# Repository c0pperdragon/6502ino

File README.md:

# 6502ino

A minimal circuit to form the environment necessary to run a 65c02 CPU.

Normally getting any form of 6502 processor to run and communicate with the outside
world is very cumbersome. In addition to the CPU and RAM you need very specific 
IO controller parts that can be hooked up to the system address and data bus.
You need a ROM for the initial boot code and some form of MMU to drive the various
selection lines according to the memory address (all IO is memory mapped).
All this leads to a pretty large and costly board even for the most basic 
program to execute.

This project tries to reduce the system size as much as possible by
using a microcontroller - in the form of an Arduino Uno - to do all the
tricky stuff. Together with only a bit of 7400 series logic and 32KB RAM,
this is  enough to get the 65c02 working with 16Mhz on a breadboard.

### Setting the fuses to generate 16Mhz on pin 8

For the setup to work, you need to configure your arduino to permanently
ouput the full system clock on a dedicated pin. This feature can not be set up
from inside a program, but needs to be done by configuring the "fuse bits". 

Setting the fuse bits is a bit complicated, but you only need to do it once. 
To access these bits, you need a dedicated programming device, called the 
AVR ISP (in-circuit-programmer). Luckily any arduino can be programmed to become 
such a device with the "ArduinoISP" example sketch that is included in the 
Arduino IDE. So you basically need a spare arduino for this process.

Wiring up the programmer arduino to the arduino being programmed can be seen in
countless internet resources. But there it is mainly done to programm a bootloader.
You need to do a different thing, for which you need the command-line tool "avrdude.exe"
which is installed along with the Arduino IDE somewhere in the depth of the "hardware/tools"
folder. 

Once everything is hooked up, open a system console and execute the following command (replace com10 
with whatever port your programmer arduino is registered in the system):
```
avrdude -p atmega328p -b 19200 -C ../etc/avrdude.conf -c avrisp -P com10
```

If everything works correctly, this will show you some status and the current settings of the
fuse bits. We are particularly interested in the value of the 'L' fuse bits, which on my
factory default Arduino Uno shows as L:FF. To set the permanent clock output, you need
to modify this value (an 8-bit value) to have the bit 6 set to 0. In my case this means

to set the 'L' fuses to BF:
```
avrdude -p atmega328p -b 19200 -C ../etc/avrdude.conf -c avrisp -P com10 -U lfuse:w:0xBF:m
```

After this settings are done, the Arduino will constantly send a 16Mhz signal on pin 8, 
no matter what, even during reset.

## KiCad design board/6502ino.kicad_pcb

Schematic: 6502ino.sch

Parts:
C1, C2, C3: 100nF; C_Disc_D3.0mm_W1.6mm_P2.50mm
C4: 10uF; C_Disc_D4.3mm_W1.9mm_P5.00mm
JANALOG1: Conn_01x06; PinSocket_1x06_P2.54mm_Vertical
JDIGITAL1: Conn_01x08; PinSocket_1x08_P2.54mm_Vertical
JDIGITAL2: Conn_01x10; PinSocket_1x10_P2.54mm_Vertical
JPOWER1: Conn_01x08; PinSocket_1x08_P2.54mm_Vertical
R1, R2, R3, R4, R5, R6, R7, R8, R9, R10: 6K8; R_Axial_DIN0207_L6.3mm_D2.5mm_P7.62mm_Horizontal
R11: 6k8; R_Axial_DIN0207_L6.3mm_D2.5mm_P7.62mm_Horizontal
R12: 100; R_Axial_DIN0207_L6.3mm_D2.5mm_P7.62mm_Horizontal
U1: W65C02S; DIP-40_W15.24mm_Socket
U2: IDT71256SA; DIP-28_W7.62mm_Socket
U3: 74AC00; DIP-14_W7.62mm_Socket

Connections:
+5V: C1.1, C2.1, C3.1, C4.1, JPOWER1.5, R11.1, U1.4, U1.6, U1.8, U1.36, U2.28, U3.14 (VCC)
/A0: U1.9, U2.10
/A1: U1.10, U2.9
/A2: U1.11, U2.8
/A3: U1.12, U2.21
/A4: U1.13, U2.7
/A5: U1.14, U2.6
/A6: U1.15, U2.23
/A7: U1.16, U2.5
/A8: U1.17, U2.24
/A9: U1.18, U2.25
/A10: U1.19, U2.26
/A11: U1.20, U2.1
/A12: U1.22, U2.2
/A13: U1.23, U2.3
/A14: U1.24, U2.4
/D0: R1.1, U1.33, U2.15
/D1: R2.1, U1.32, U2.16
/D2: R3.1, U1.31, U2.13
/D3: R4.1, U1.30, U2.17
/D4: R5.1, U1.29, U2.12
/D5: R6.1, U1.28, U2.18
/D6: R10.1, U1.27, U2.11
/D7: R9.1, U1.26, U2.19
/IOBUSY: JDIGITAL1.8, R11.2, U3.12
/IOSELECT: R8.1, U1.25, U2.20, U3.13
/PHI2: JDIGITAL2.1, U1.37, U3.4, U3.5, U3.10
/RWB: R7.1, U1.34, U3.1, U3.2
/_RESET: JPOWER1.3, U1.40
GND: C1.2, C2.2, C3.2, C4.2, JDIGITAL2.7, JPOWER1.6, JPOWER1.7, U1.21, U1.38, U2.14, U3.7 (GND)
unnamed: JANALOG1.1, R1.2
unnamed: JANALOG1.2, R2.2
unnamed: JANALOG1.3, R3.2
unnamed: JANALOG1.4, R4.2
unnamed: JANALOG1.5, R5.2
unnamed: JANALOG1.6, R6.2
unnamed: JDIGITAL1.4, R10.2
unnamed: JDIGITAL1.5, R9.2
unnamed: JDIGITAL1.6, R8.2
unnamed: JDIGITAL1.7, R7.2
unnamed: R12.1, U1.2
unnamed: R12.2, U3.11
unnamed: U2.22, U3.6
unnamed: U2.27, U3.8
unnamed: U3.3, U3.9

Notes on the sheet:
(32 KB RAM)
(CPU)

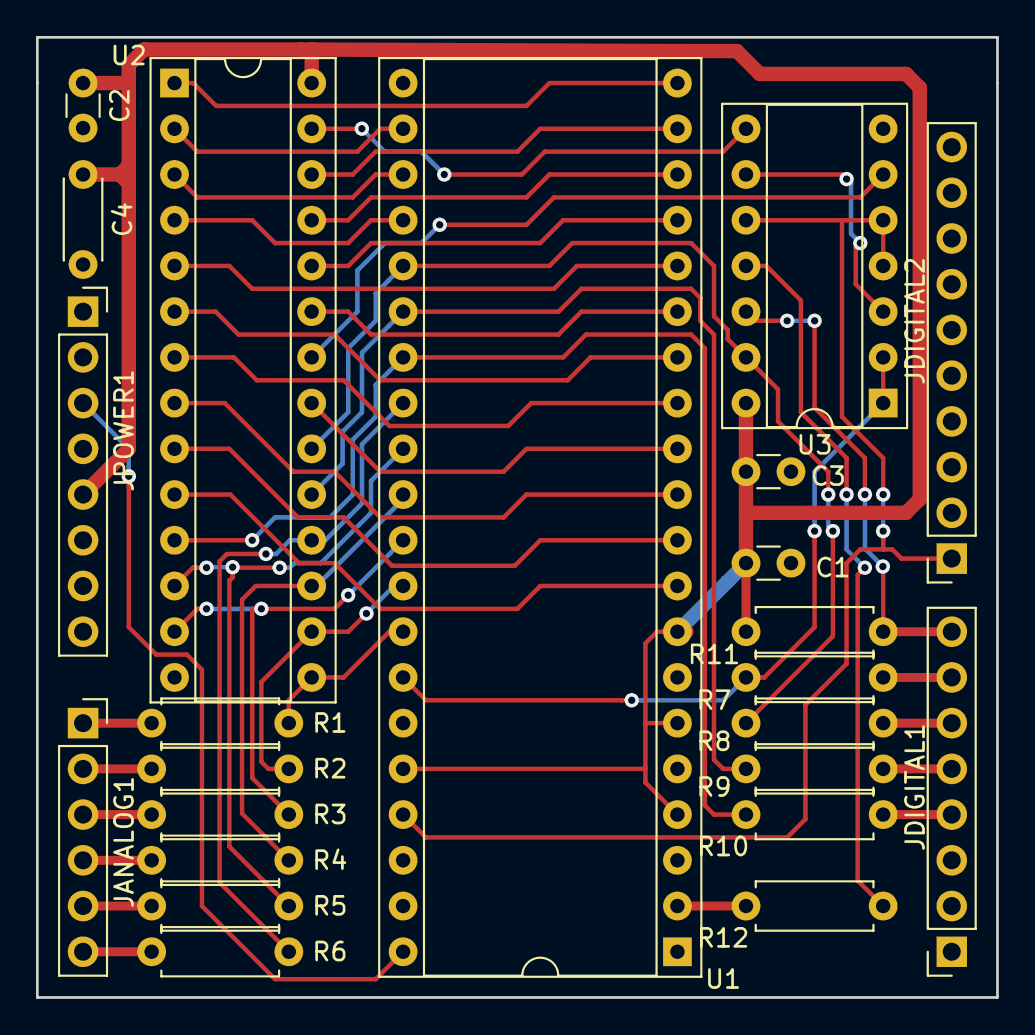
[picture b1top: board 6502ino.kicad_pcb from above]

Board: 2 copper layers, 53.3 x 53.3 mm, 23 parts (0 on the bottom side), 45 nets.

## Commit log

2019-08-31 First schematics and PCB
2019-09-14 Reduce number of ICs to 3, first working arduino sketch
2019-09-18 Fiddling with the layout
2019-09-20 PCB layout Rev. 1
2019-10-03 Fix: Connect BE to +5V
